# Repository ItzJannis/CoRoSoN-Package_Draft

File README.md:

# CoRoSoN-Package Draft
>**Co**|mponents for \
>**Ro**|bocupJunior \
>**So**|ccer \
> **N**|ewcomers \
> Project: [CoRoSoN-Kit](https://github.com/CoRoSoN-Kit/CoRoSoN-Kit) \
> Competition: [RoboCup](https://www.robocup.org) \
> Author: [BohleBots](https://www.bohlebots.de)

# Description
This project offers a draft version to the official [CoRoSoN-Kit](https://github.com/CoRoSoN-Kit/CoRoSoN-Kit) to provide the fundamental building blocks for a fully functional robot participating in the Soccer Junior division of the [RoboCup](https://www.robocup.org). \
The purpose is to allow for an newcomer friendly entry to the competition by wrapping the essential functions with easy to use APIs. Board designs are designed to be rebuild easily and affordable. \
\
Feel free to reach out to us for questions, feedback, suggestions or constructive critism! \
See you in the competition!

## Disclaimer
The software and the hardware designs are developed to the best of our knowledge to serve the intented purpose, but may still contain faults. Our software and hardware are provided "as is" and do not provide any warranty. The risk of using it and all neccessary servicing, repair and correction as well as their cost is with you.

# Makefile
Using the Arduino IDE or arduino-cli requires all source for a .ino sketch to be inside the sketch folder or inside the libaries directory of the Arduino installation. \
Therefore source files inside Software/Shared or Software/Peripheral, that are not located directly next to a .ino sketch, cause problems. \
To allow for easy compatibility of this project with Arduino the Makefile was created. \
It automates the generation of valid Arduino sketch folders, such that they can be opened in the Arduino IDE or used with arduino-cli. \
\
The Makefile does not require all source files to be inside the sketch folder, but it requires SketchName.ino to be located inside Software/SketchName/.
\
Run `make` inside the home directory of this repo to see all the options.

# Software
## Requirements
1. [Arduino](https://www.arduino.cc/)
2. [Espressif ESP32 Board Information](https://github.com/espressif/arduino-esp32)
3. [elapsedMillis](https://github.com/pfeerick/elapsedMillis/wiki)
4. [PixyI2C](https://pixycam.com/downloads-pixy1/)
5. [Pixy2I2C](https://pixycam.com/downloads-pixy2/)

## Shared
Software that is not build for a specific board but is shared across different board's software.

### CoRoSoN_Util
Providing usefull utility definitions for error handling, initializing data and better debugging. \
The `enum ERROR_CODE` provides bitflags for uniform error handling while `DEBUG_PRINT(Variable)`, `DEBUG_ERRORS(Errors)` and `DEBUG_BLOCK(Message, NumMillis)` provide easier debugging via the serial connection and the `MIN(X,Y)`, `MAX(X,Y)`, `ABS(X)`, `ARRAY_LENGTH(Arr)`, `ZEROMEM(Obj)` provide function-like macros to handle data without tedious reimplementation of often used functionalities.

### CoRoSoN_I2C
Providing a simpler, more beginner friendly interface to work with the I2C bus system used in this project. \
`I2C_Init()`, `I2C_TestConnection()`, `I2C_Write()` and `I2C_ReadBlocking()` provide all the functionality a newcomer robot for the competition needs. \
**Attention**: \
`I2C_ReadBlocking()` waits for the answers and is therefore **blocking** the execution of the program. \
Make sure that NumBytes equals the length of the passed byte array!

### CoRoSoN_Vector
Providing `class Vector` to easily compute vectorial calculations with functions and operator overloading.

### CoRoSoN_Config
This file defines the hardware configuration (namely the pins) for the software.

## Main
Software that is supposed to be used on the mainboard.
### CoRoSoN_Main
The definitions of `enum COLOR`, `enum SIDE`, `enum I2C_ADD_BTNLED_MODULE`, `enum MOTOR` and `enum DIRECTION` are used to firstly make software better readable for newcomers and secondly somehow restrict inputs to reduce buggy behavior due to occasionally wrong inputs. \
`CoRoSoN_Init()`, `CoRoSoN_SetLEDColor()`, `CoRoSoN_ButtonIsPressed()` and `CoRoSoN_SetMotor()` provide a beginner friendly API to setting the mainboard up in the `setup()` of an arduino program as well as reading and writing the mainboards pins.

## Peripheral
Software that is supposed to be used on the mainboard to make use of the peripheral devices.
### CoRoSoN_Eeprom
Providing an interface to the ESP32's eeprom which is easy to use.\
The eeprom is very usefull to save backup data about the current program state (i.e. the robot is enabled to drive) in case of a shutdown or a reset for whatever reason.\
The `struct EEPROM_DATA` can be filled with whatever you want to read / write from the eeprom.
`EEPROM_Init()`, `EEPROM_Read()` and `EEPROM_Write()` provide an easy interface that only deals with instances of `EEPROM_DATA`.

### CoRoSoN_Pixy
Providing `class Pixy` with its `Update()`, `GoalSeen()`, `OwnGoalSeen()`, `GoalDirection()` and `OwnGoalDirection()` to make use of the Pixy camera for locating the two goals on the playing field. \
In `CoRoSoN_Pixy.h` set `PIXY_VERSION` to 1 or 2 according to the version of the Pixy cam in use. \
For the directions: <0 represents left, >0 represents right

### CoRoSoN_IR-Ring
Providing `class IRRing` with its `Update()`, `BallSeen()`, `BallDirection()` and `BallDistance()` to make use of the infrared sensor ring with the firmware running on it (also provided).
For the directions: <0 represents left, >0 represents right, 0 represents front, -32 represents no ball seen
For the distance: 1...32 represents closest...furthest, 0 represents no ball seen

## IR
Software that is supposed to be used on the infrared sensor ring.
### Firmware_IR-Ring
Providing the firmware that is designed to be loaded onto the infrared sensor ring and making it ready to be used in a plug-and-play manner. \
#### Software Process / Algorithm
1. Read all physical signals
2. Remove minimum value from all sensor values (ensuring at least one is 0)
3. Use exponential moving average (EMA) for each sensor - the lower `EMA_ALPHA_PERCENTAGE`, the more the values are smoothed
4. Gaussian blur on each sensors value with its 2 neighbouring values - `BLUR_ORIGINAL_VALUE_WEIGHT_PERCENTAGE` defines the weight the middle sensor gets
5. Exaggerate differences by squaring percentage of maximum value for each sensor
6. Expand values to higher resolution by using cubic interpolation
7. Giving the sensors close to the last output direction a boost of up to 5% of their current value, to reduce fluctuations
8. Find highest value
9. Exaggerate differences by squaring percentage of maximum value for each sensor
10. Vector addition around highest value for more precise direction - `VECTOR_ADDITION_SENSOR_COUNT` defines the number of vectors involved
11. Determine distance by numeric integration
12. Compute final direction and distance with running median - `RUNNING_MEDIAN_DIRECTION_LENGTH` and `RUNNING_MEDIAN_DISTANCE_LENGTH` define the history length for the running medians

# Hardware
## Main
Contains the [KiCad](https://www.kicad.org/download/) project of the Main PCB. 

## IR-Ring
Contains the [KiCad](https://www.kicad.org/download/) project of the IR-Ring PCB. 

## 3D_Prints
Contains all the 3D printable designs as .stl files.

### CasterBall
Spherical third ground contact point to prevent the robot from falling over due to having only 2 wheels.
### Chassis_Base
The base part of the chassis fitting together with the top plate.
### Chassis_TopPlate
The main plate enclosing the chassis, also including part of the machanism to hold the battery pack.
### Dribbler_Enclosure
Holds the dribbling unit (motor and rotating silicone shell).
### Dribbler_Enclosure_EndCap
The end cap to close the enclosure of the dribbling unit.
### Dribbler_Mounting
Add-On to the top plate to mount the dribbling unit and support the IR-Ring up on top.
### Dribbler_Mounting_short
Shorter version of Dribbler_Mounting.stl in terms of height.
### Dribbler_SiliconeRoller
Rotating shell of the dribbling unit, supposed to be covered with silicone.
### IR-Ring_Cover
Covers the IR-Ring PCB to reduce external ambient noise for the sensors.
### IR-Ring_Cover_Counterpart
Counterpart for the IR-Ring cover such that it is properly fixated.
### Main_Frame
Mounting frame for the Main PCB.
### Motor_Mounting
Mounting for the 2 motors that move the robot.
### Pixy_Mounting
Mounting frame for pixy camera.
### WheelCoupling_Direct
Coupling adapter to connect the rotating shell to the motor axis.
### WheelCoupling_Insert
Coupling adapter to connect the wheels to the motor axis.

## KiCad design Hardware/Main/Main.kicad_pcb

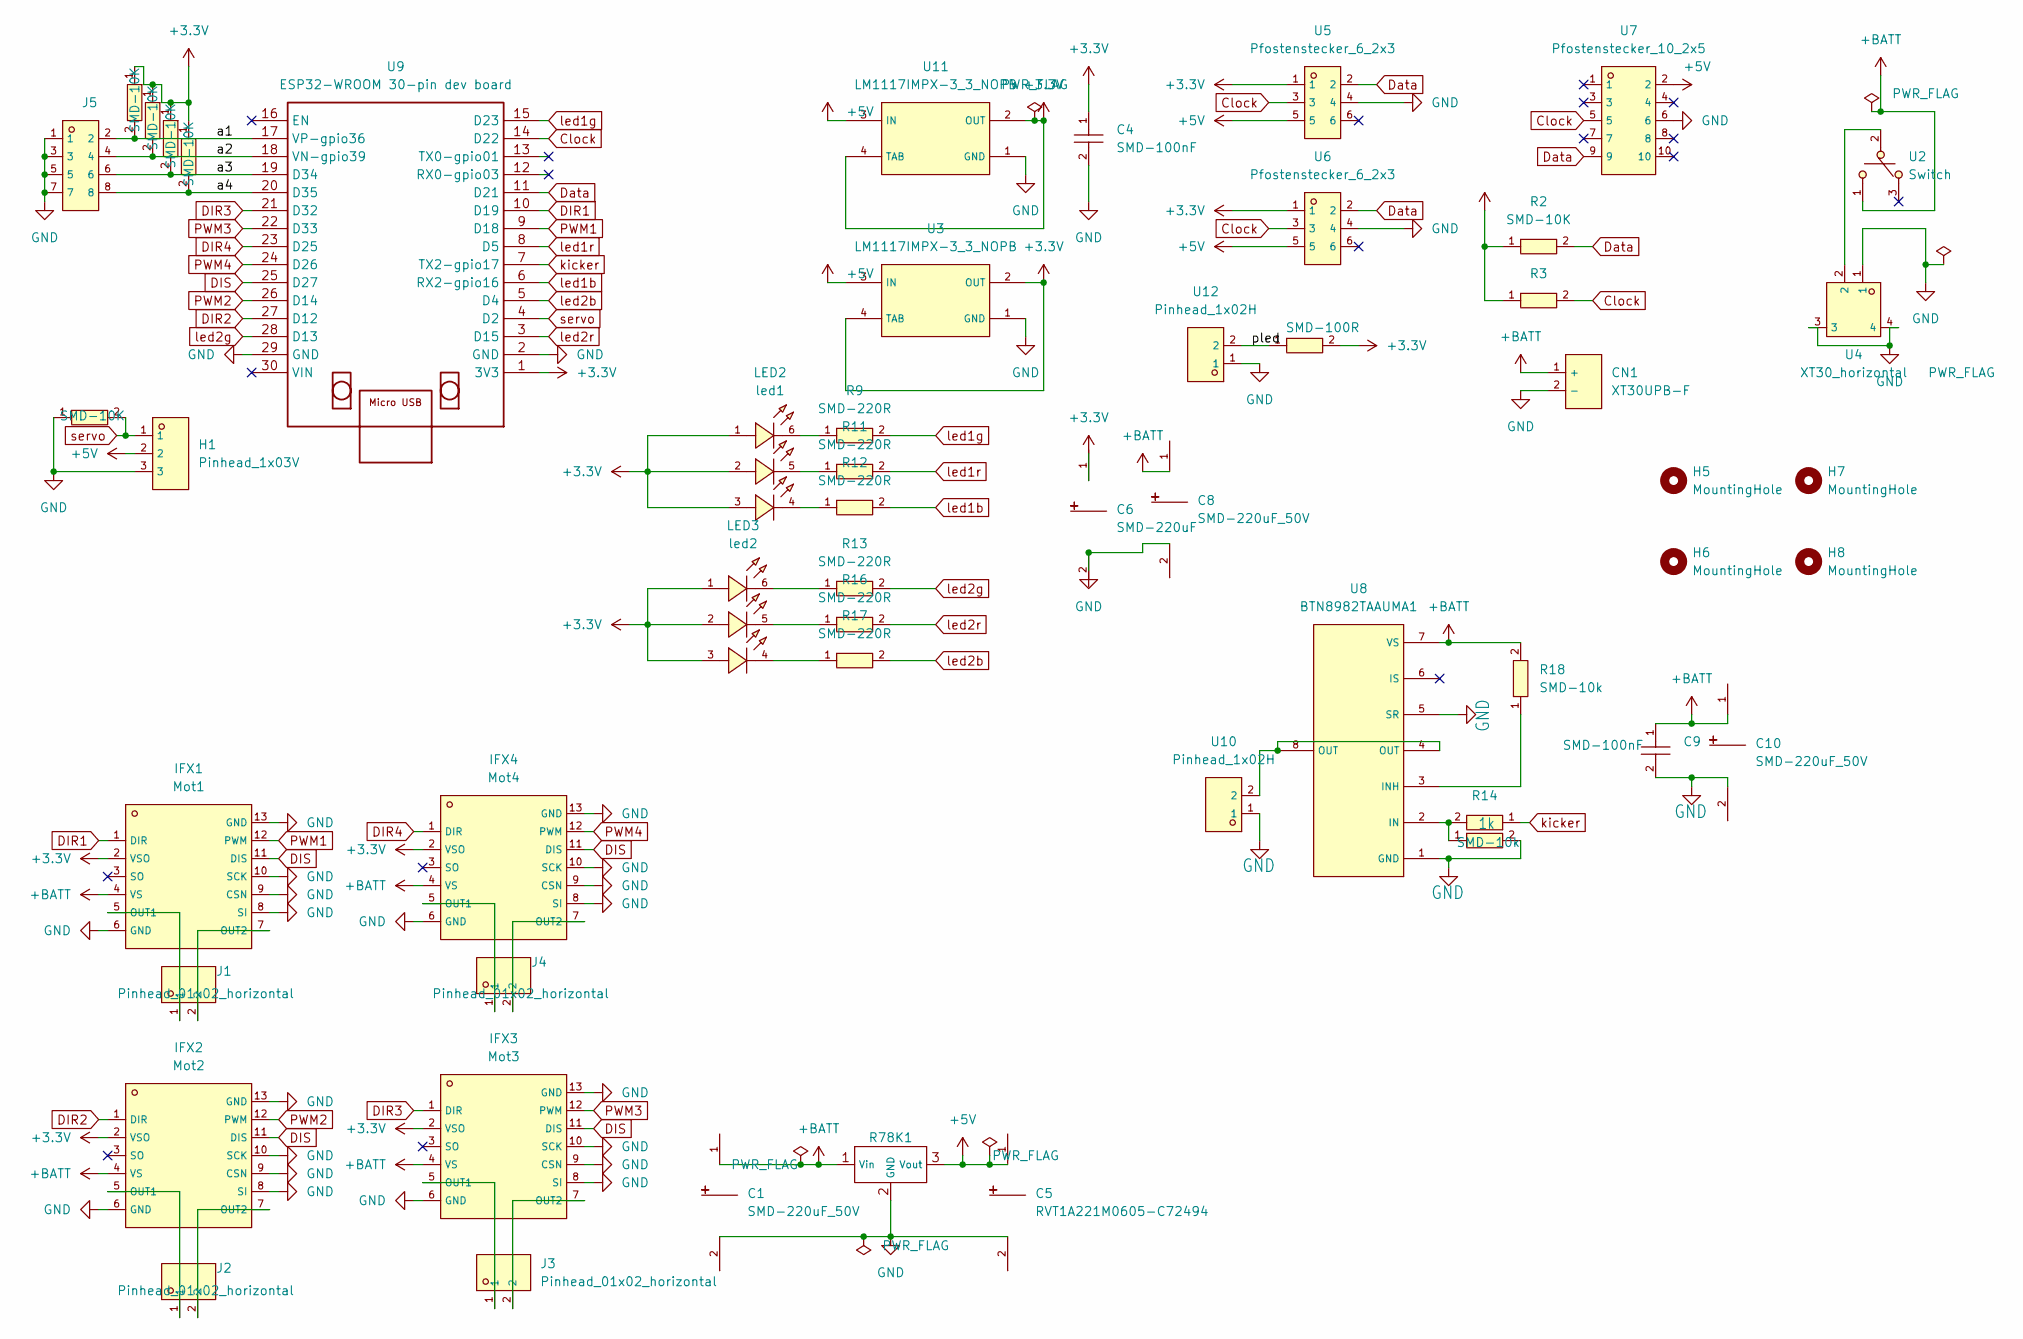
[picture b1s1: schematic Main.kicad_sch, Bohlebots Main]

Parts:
C1, C8, C10: SMD-220uF_50V; CAP-SMD_BD10.0-L10.3-W10.3-LS11.3-FD; LCSC C125977
C4, C9: SMD-100nF; C0603; LCSC C30926
C5: RVT1A221M0605-C72494; CAP-SMD_BD10.0-L10.3-W10.3-LS11.3-FD; LCSC C125977
C6: SMD-220uF; CAP-SMD_BD10.0-L10.3-W10.3-LS11.3-FD; LCSC C125977
CN1: XT30UPB-F; CONN-TH_XT30UPB-F; LCSC C108769
H1: Pinhead_1x03V; HDR-TH_3P-P2.54-V-M-1; LCSC C7501261
H5, H6, H7, H8: MountingHole; MountingHole_4.3mm_M4
IFX1: Mot1; SO-12_L6.4-W7.5-P1.00-LS10.3-BL-EP; LCSC C112633
IFX2: Mot2; SO-12_L6.4-W7.5-P1.00-LS10.3-BL-EP; LCSC C112633
IFX3: Mot3; SO-12_L6.4-W7.5-P1.00-LS10.3-BL-EP; LCSC C112633
IFX4: Mot4; SO-12_L6.4-W7.5-P1.00-LS10.3-BL-EP; LCSC C112633
J1, J2, J3, J4: Pinhead_01x02_horizontal; HDR-TH_2P-P2.54-H-M-W10.4; LCSC C492410
J5: Conn_02x04_Row_Letter_First; HDR-TH_8P-P2.54-H-M-R2-C4-S2.54; LCSC C706885
LED2: led1; LED-SMD_6P-L5.0-W5.0-TL_TC5050RGBF08; LCSC C784540
LED3: led2; LED-SMD_6P-L5.0-W5.0-TL_TC5050RGBF08; LCSC C784540
R2, R3, R5, R6, R7, R10, R15: SMD-10K; R0603; LCSC C25804
R8: SMD-100R; R0603; LCSC C22775
R9, R11, R12, R13, R16, R17: SMD-220R; R0603; LCSC C217883
R14, R18: SMD-10k; R0603; LCSC C25804
R23: 1k; R0603; LCSC C22548
R78K1: R785K
U2: Switch; SW-TH_MT-0-103-A101-M200-RS; LCSC C1788498
U3, U11: LM1117IMPX-3_3_NOPB; SOT-223_L6.5-W3.5-P2.30-LS7.0-BR; LCSC C23984
U4: XT30_horizontal; CONN-TH_XT30PW-M; LCSC C431092
U5, U6: Pfostenstecker_6_2x3; HDR-TH_6P-P2.54-V-F-R2-C3-S2.54-4; LCSC C5372863
U7: Pfostenstecker_10_2x5; HDR-TH_10P-P2.54-V-F-R2-C5-S2.54-5; LCSC C5372865
U8: BTN8982TAAUMA1; TO-263-7_L10.2-W10.4-P1.27-LS14.4-TL; LCSC C74175
U9: ESP32-WROOM 30-pin dev board; MODULE_ESP32_DEVKIT_V1
U10, U12: Pinhead_1x02H; HDR-TH_2P-P2.54-H-M-W10.4; LCSC C492410

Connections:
+3.3V: C4.1, C6.1, IFX1.2 (VSO), IFX2.2 (VSO), IFX3.2 (VSO), IFX4.2 (VSO), LED2.1 (+), LED2.2 (+), LED2.3 (+), LED3.1 (+), LED3.2 (+), LED3.3 (+), R2.1, R3.1, R5.1, R6.1, R7.1, R8.2, R10.1, U3.2 (OUT), U3.4 (TAB), U5.1, U6.1, U9.1 (3V3), U11.2 (OUT), U11.4 (TAB)
+5V: C5.1, H1.2, R78K1.3 (Vout), U3.3 (IN), U5.5, U6.5, U7.2, U11.3 (IN)
+BATT: C1.1, C8.1, C9.1, C10.1, CN1.1 (+), IFX1.4 (VS), IFX2.4 (VS), IFX3.4 (VS), IFX4.4 (VS), R18.2, R78K1.1 (Vin), U2.1, U8.7 (VS)
/a1: J5.2, R5.2, U9.17 (VP-gpio36)
/a2: J5.4, R6.2, U9.18 (VN-gpio39)
/a3: J5.6, R7.2, U9.19 (D34)
/a4: J5.8, R10.2, U9.20 (D35)
/pled: R8.1, U12.2
Clock: R3.2, U5.3, U6.3, U7.5, U9.14 (D22)
DIR1: IFX1.1 (DIR), U9.10 (D19)
DIR2: IFX2.1 (DIR), U9.27 (D12)
DIR3: IFX3.1 (DIR), U9.21 (D32)
DIR4: IFX4.1 (DIR), U9.23 (D25)
DIS: IFX1.11 (DIS), IFX2.11 (DIS), IFX3.11 (DIS), IFX4.11 (DIS), U9.25 (D27)
Data: R2.2, U5.2, U6.2, U7.9, U9.11 (D21)
GND: C1.2, C4.2, C5.2, C6.2, C8.2, C9.2, C10.2, CN1.2 (-), H1.3, IFX1.6 (GND), IFX1.8 (SI), IFX1.9 (CSN), IFX1.10 (SCK), IFX1.13 (GND), IFX2.6 (GND), IFX2.8 (SI), IFX2.9 (CSN), IFX2.10 (SCK), IFX2.13 (GND), IFX3.6 (GND), IFX3.8 (SI), IFX3.9 (CSN), IFX3.10 (SCK), IFX3.13 (GND), IFX4.6 (GND), IFX4.8 (SI), IFX4.9 (CSN), IFX4.10 (SCK), IFX4.13 (GND), J5.1, J5.3, J5.5, J5.7, R14.2, R15.1, R78K1.2 (GND), U3.1 (GND), U4.1, U4.3, U4.4, U5.4, U6.4, U7.6, U8.1 (GND), U8.5 (SR), U9.2 (GND), U9.29 (GND), U10.1, U11.1 (GND), U12.1
unnamed: IFX1.5 (OUT1), J1.1
unnamed: IFX1.7 (OUT2), J1.2
unnamed: IFX2.5 (OUT1), J2.1
unnamed: IFX2.7 (OUT2), J2.2
unnamed: IFX3.5 (OUT1), J3.1
unnamed: IFX3.7 (OUT2), J3.2
unnamed: IFX4.5 (OUT1), J4.1
unnamed: IFX4.7 (OUT2), J4.2
unnamed: LED2.4 (-), R12.1
unnamed: LED2.5 (-), R11.1
unnamed: LED2.6 (-), R9.1
unnamed: LED3.4 (-), R17.1
unnamed: LED3.5 (-), R16.1
unnamed: LED3.6 (-), R13.1
unnamed: U2.2, U4.2
unnamed: R14.1, R23.2, U8.2 (IN)
unnamed: R18.1, U8.3 (INH)
unnamed: U8.4 (OUT), U8.8 (OUT), U10.2
PWM1: IFX1.12 (PWM), U9.9 (D18)
PWM2: IFX2.12 (PWM), U9.26 (D14)
PWM3: IFX3.12 (PWM), U9.22 (D33)
PWM4: IFX4.12 (PWM), U9.24 (D26)
kicker: R23.1, U9.7 (TX2-gpio17)
led1b: R12.2, U9.6 (RX2-gpio16)
led1g: R9.2, U9.15 (D23)
led1r: R11.2, U9.8 (D5)
led2b: R17.2, U9.5 (D4)
led2g: R13.2, U9.28 (D13)
led2r: R16.2, U9.3 (D15)
servo: H1.1, R15.2, U9.4 (D2)

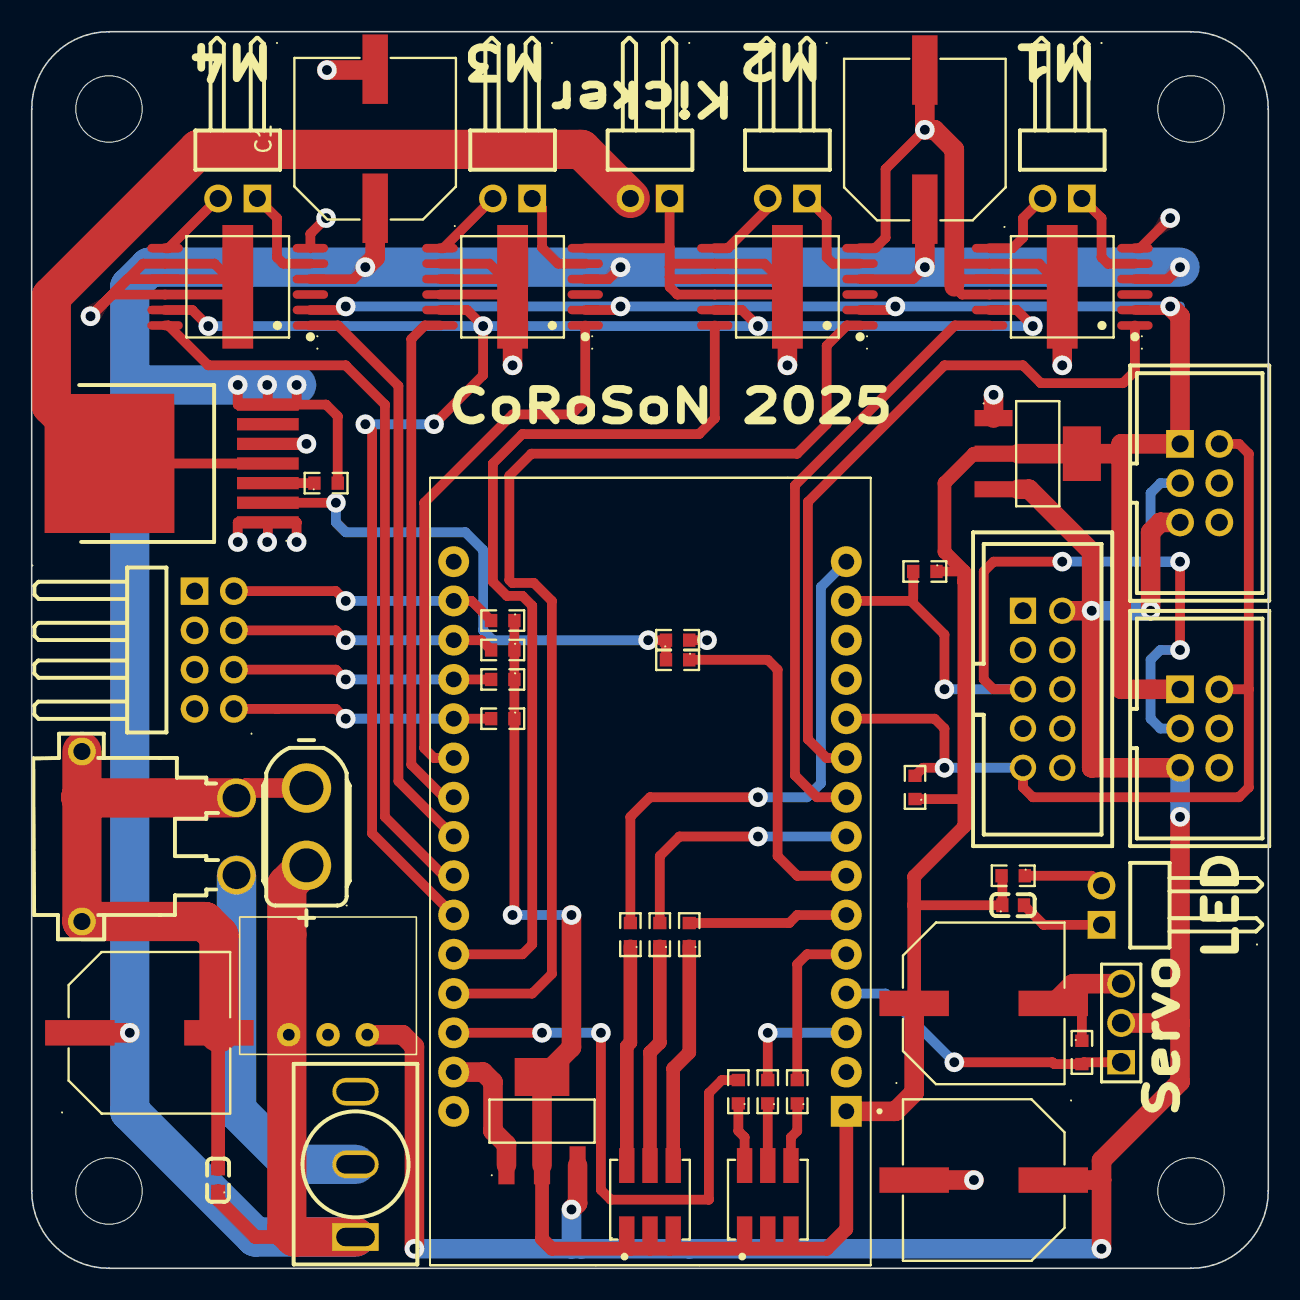
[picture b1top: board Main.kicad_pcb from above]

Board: 2 copper layers, 80.0 x 80.0 mm, 53 parts (0 on the bottom side), 46 nets.

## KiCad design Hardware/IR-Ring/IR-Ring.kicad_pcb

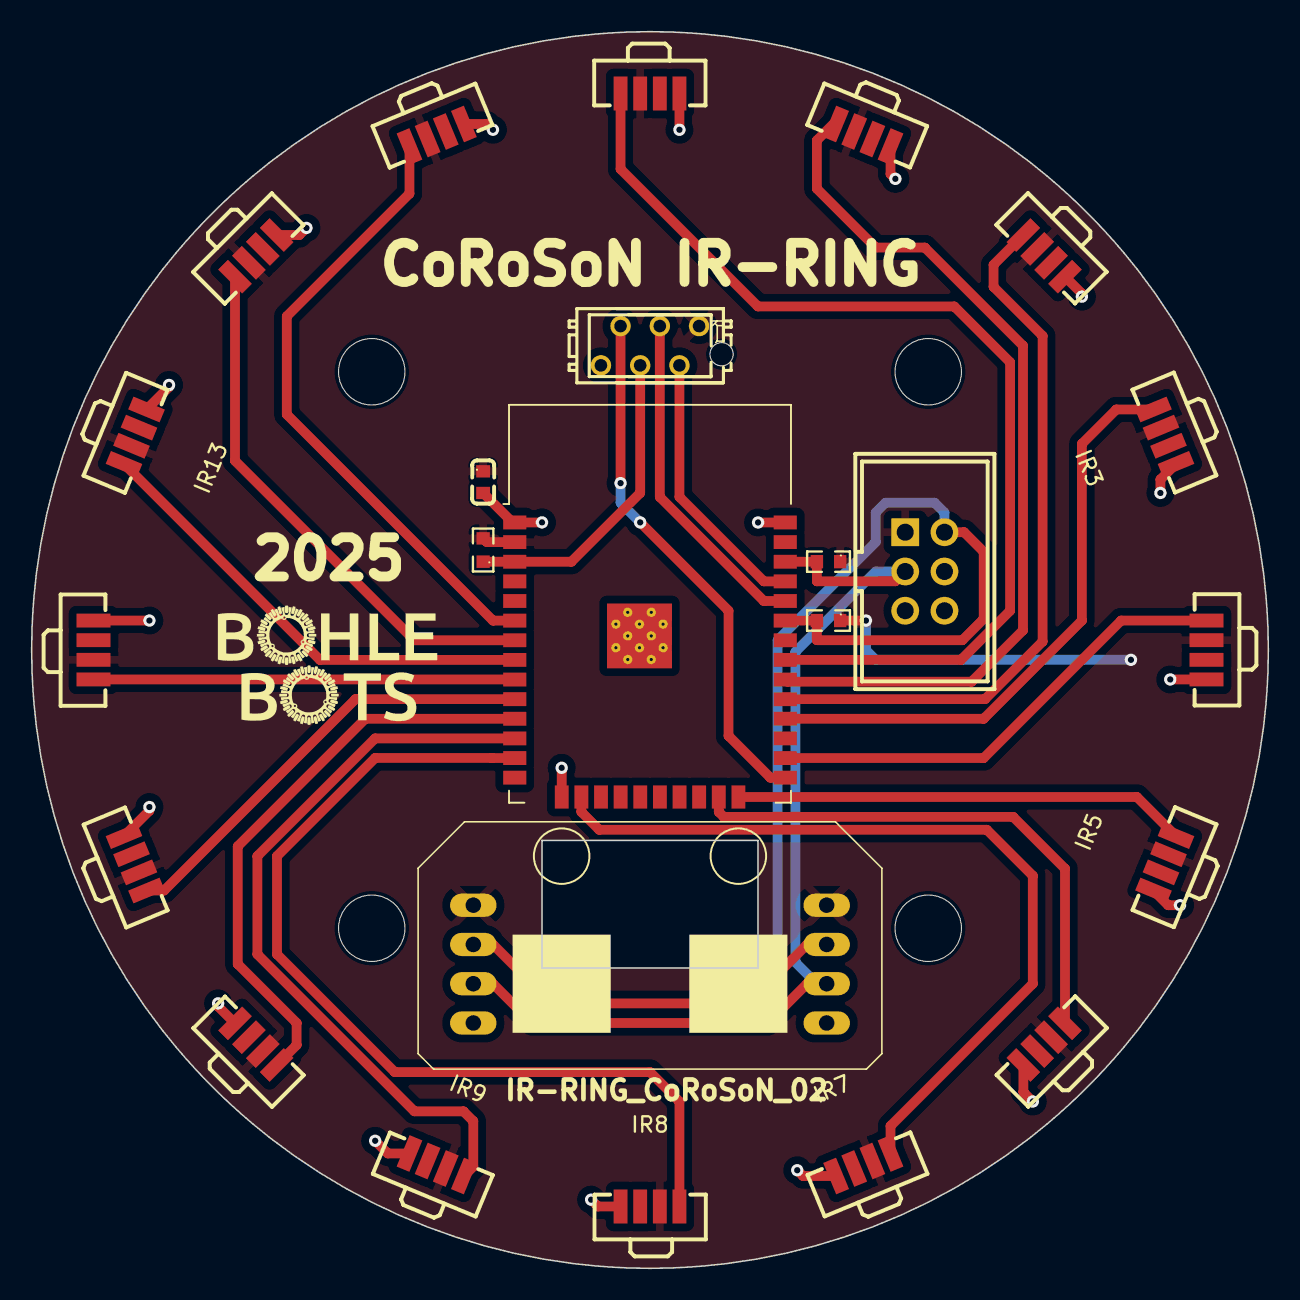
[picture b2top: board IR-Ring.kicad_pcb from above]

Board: 2 copper layers, 80.0 x 80.0 mm, 28 parts (0 on the bottom side), 24 nets.

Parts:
C2: SMD-1uF; C0603
H1, H2, H3, H4: MountingHole; MountingHole_4.3mm_M4
IR0, IR1, IR2, IR3, IR4, IR5, IR6, IR7, IR8, IR9, IR10, IR11, IR12, IR13, IR14, IR15: TSSP6038TR; SENSOR-SMD_TSSP6038TR
R1, R2, R3: SMD-10k; R0603
Taster_LED1: TASTER_LED
U1: ESP32-WROOM-32; ESP32-WROOM-32-small
U2: Pfostenstecker_6_2x3; HDR-TH_6P-P2.54-V-F-R2-C3-S2.54-4
X1: MICROMATCH-6

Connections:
+3.3V: C2.1, IR0.3 (VS), IR1.3 (VS), IR2.3 (VS), IR3.3 (VS), IR4.3 (VS), IR5.3 (VS), IR6.3 (VS), IR7.3 (VS), IR8.3 (VS), IR9.3 (VS), IR10.3 (VS), IR11.3 (VS), IR12.3 (VS), IR13.3 (VS), IR14.3 (VS), IR15.3 (VS), R1.2, R2.1, R3.1, Taster_LED1.1 (v+), Taster_LED1.8, U1.2 (VDD), U2.1, X1.1
Boot: U1.25 (IO0), X1.5
Clock: R3.2, Taster_LED1.3 (Clock), Taster_LED1.6, U1.36 (IO22), U2.3
D1: IR0.4 (OUT), U1.31 (IO19)
D2: IR1.4 (OUT), U1.30 (IO18)
D3: IR2.4 (OUT), U1.29 (IO5)
D4: IR3.4 (OUT), U1.28 (IO17)
D5: IR12.4 (OUT), U1.9 (IO33)
D6: IR13.4 (OUT), U1.8 (IO32)
D7: IR14.4 (OUT), U1.7 (IO35)
D8: IR15.4 (OUT), U1.6 (IO34)
D9: IR4.4 (OUT), U1.26 (IO4)
D10: IR5.4 (OUT), U1.24 (IO2)
D11: IR6.4 (OUT), U1.23 (IO15)
D12: IR7.4 (OUT), U1.16 (IO13)
D13: IR8.4 (OUT), U1.13 (IO14)
D14: IR9.4 (OUT), U1.12 (IO27)
D15: IR10.4 (OUT), U1.11 (IO26)
D16: IR11.4 (OUT), U1.10 (IO25)
Data: R2.2, Taster_LED1.2 (Data), Taster_LED1.7, U1.33 (IO21), U2.2
EN: R1.1, U1.3 (EN), X1.4
GND: C2.2, IR0.1 (GND), IR1.1 (GND), IR2.1 (GND), IR3.1 (GND), IR4.1 (GND), IR5.1 (GND), IR6.1 (GND), IR7.1 (GND), IR8.1 (GND), IR9.1 (GND), IR10.1 (GND), IR11.1 (GND), IR12.1 (GND), IR13.1 (GND), IR14.1 (GND), IR15.1 (GND), Taster_LED1.4 (GND), Taster_LED1.5, U1.1 (GND), U1.15 (GND), U1.38 (GND), U1.39 (GND), U2.4, X1.6
RX: U1.34 (RXD0/IO3), X1.3
TX: U1.35 (TXD0/IO1), X1.2

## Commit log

2023-09-26 Initial files created
2023-09-26 CoRoSoN: include other CoRoSoN modules
2023-09-26 Package now arduino compatible
2023-09-26 added gitignore
2023-09-26 Ignore .vcode folder
2023-09-26 Filled .h files with general file structure
2023-10-03 modified file header
2023-10-03 Util: buil up from BB_BASE
2023-10-03 ArduinoFile uses CoRoSoN_Util
2023-10-03 Added eeprom
2023-10-03 Implemented compass based on BohleBots header
2023-10-03 Pixy
2023-10-13 ZEROFILL => ZEROMEM
2023-10-15 "BB_DEBUG" => "COROSON_DEBUG"
2023-10-15 Implemented I2C module
2023-10-15 Compass uses I2C module
2023-10-15 Compass use EnsureInit()
2023-10-15 I2C cleanup
2023-10-27 Added IRRing
2023-10-27 Main header as bundle of other modules
2023-10-29 CoRoSoN main header now has functionality
2023-10-29 Changed file header comments
2023-12-13 ERRORS as typedef instead of define
2023-12-13 minor changes and improvements
2024-07-01 Implemented UNTESTED Firmware for IR Ring
2024-07-01 Added .ino file for IR Ring Firmware
2024-07-03 Last bugfixes to allow testing
2024-07-03 small bugfix: "ERROR" => "ERRORS"
2024-07-04 Bugfix: "_aRawValues" => "aRawValues"
2024-07-05 Minor bugfixes
2024-07-05 Values now expanded
2024-07-06 Cubic interpolation
2024-07-06 Fixed compiler errors and warnings
2024-07-07 Bugfix: TotalSum was not set
2024-07-07 Explicit 0.0 instead of 0 for init of double TotalSum
2024-08-19 Changed formatting slightly
2024-08-19 More code formatting
2024-08-21 Added README.md
2024-08-30 Bugfix in macro definition
2024-08-30 IR-Ring now performs vector addition around highest value for more precise and robust direction
2024-09-02 IR Ring config more user friendly and tested
2024-09-06 Fixed typo in a comment
2024-09-17 Split config of CoRoSoN.h into CoRoSoN_Config.h to seperate it from main board code for ir firmware
2024-09-17 Added license
2024-09-17 Modified README to show CoRoSoN_Config
2024-09-30 Changed defines to please arduino
2024-10-01 Fixed comment
2024-10-15 Added CoRoSoN_Vector
2024-10-15 Updated file organization into subfolders
2024-10-15 Updated gitigore to adapt to new file structure
2024-11-13 Firmware_IR-Ring: fixed config errors
2024-12-12 Fixed IRRing::Update() conversion from read value to signed direction
2024-12-13 Bitshifts for ERROR enum instead of binary numbers
2024-12-13 Use of BLUR_ORIGINAL_VALUE_WEIGHT_PERCENTAGE was wrong. Fixed. + minor comment changes
2024-12-13 IR Firmware: Fixed shift when expanding values
2024-12-31 Pins were shifted by 1 to the left and therefore wrong. Fixed.
2024-12-31 changed arrays for blurred and expanded values from double to int
2025-01-06 Changes to be upto date with feedback of first team
2025-01-08 Reworked README and "Src" renamed to "Software"
2025-01-09 Typos fixed
2025-01-10 RunningMedian.h removed for self-written Exponential Moving Average
2025-01-12 IR-Firmware: indices were off. Fixed.
2025-01-17 IRRing class constructor no longer tests I2C to allow call before setup()
2025-01-17 Updated Config and Main to adapt to new MainBoard
2025-01-20 Modified default defines in IR Firmware to smaller PCB
2025-01-24 Configuration of IR Firmware defines explained in README
2025-01-25 Added preprocessor sanity checks for EMA config defines
2025-01-25 Cubic interpolation changed to linear interpolation
2025-01-25 Version for using a Grid-Heatmap for ball likelihood. Compilable. TOO BIG for Esp32.
2025-01-26 EMA for each sensor + running median for overall direction and distance
2025-02-02 Added difference exaggeration as well as boost close to last output direction
2025-02-08 Distance improved by changing calculation method.
2025-02-08 I2C fixed. - Demo build for LEDs, buttons and motor working
2025-02-25 I2C fixed - demo build for LEDs, buttons and motor working
2025-02-25 Changed link to CoRoSoN-Kit from github profile to actual repository.
2025-02-26 .ino files are not ignored anymore
2025-02-26 Added Main.ino - Only tests the IR-Ring and CoRoSoN_Main so far.
2025-02-26 "IR" -> "IR-Ring" and added IR-Ring.ino
2025-02-27 Added Subfolder for generated arduino sketches to .gitignore
2025-02-28 Added Makefile for easy use with Arduino IDE and arduino-cli.
2025-02-28 Removed Compass completely.
2025-02-28 Typo in Makefile fixed
2025-02-28 Initial structure for using Pixy1.
2025-02-28 PixyI2C.h and Pixy2I2C.h can not be used at the same time => Preprocessor handles it.
2025-03-06 IR: Fixed underflow of _BallDir
2025-03-06 PixyV1 and Pixy2 working properly
2025-03-06 Modified IR Firmware defines for wide PCB with cover similar to the one for the small PCB
2025-03-11 Added KiCad projects of Main and IR-Ring PCB to repo.
2025-03-11 Changed distance calculation for improvement on wide ring
2025-03-20 Function names more uniform.
2025-03-20 Modified Main.ino to include everything necessary except a game strategy.
2025-03-27 Added 3D print designs to the Hardware folder.
2025-05-19 Added boosting of front sensors by the 4 additional (previously unused) sensors.
2025-05-22 Updated pcb design of main board
2025-06-25 Hardware/3D_Prints updated: added missing second part of the chassis as well as motor mountings + renamed some files
